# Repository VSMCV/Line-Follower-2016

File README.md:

# Line-Follower-2016
Hardware design and software files for a PID line follower robot.

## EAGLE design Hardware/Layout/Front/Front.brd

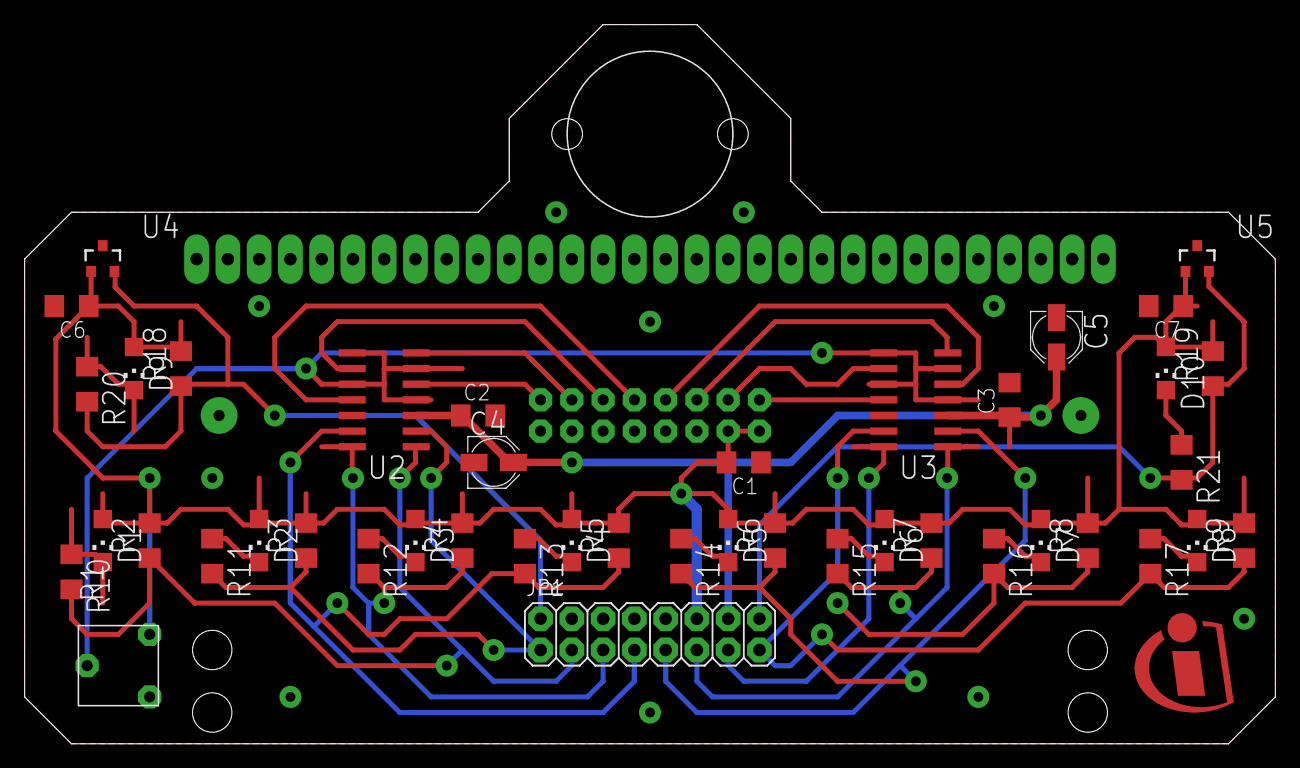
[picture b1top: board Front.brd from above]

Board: 2 copper layers, 101.6 x 58.4 mm, 47 parts (1 on the bottom side), 32 nets.

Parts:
BALL1: BALL
C1, C2, C3, C6, C7: C_NONPOL100NF; C1206
C4, C5: C-POL10UF; PANASONIC_B
D1, D2, D3, D4, D5, D6, D7, D8, D9, D10: LED; CHIPLED_1206
JP1: 2X08
JP2: 1X30
R1: R-TRIMMER; TRIMMER
R2, R3, R4, R5, R6, R7, R8, R9, R18, R19: 12k; R1206
R10, R11, R12, R13, R14, R15, R16, R17, R20, R21: 470R; R1206
U1: SENSOR_BAR_QTR-8ASENSOR_BAR; QTR-8A
U2, U3: LM339; SO14
U4, U5: TLE4964-6M; SOT23-3
U$1: INFINEON_LOGO_INFINEON_ICON_8

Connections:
+3V3: C1.2, C6.1, C7.1, D1.A, D2.A, D3.A, D4.A, D5.A, D6.A, D7.A, D8.A, D9.A, D10.A, JP1.12, R1.2, R2.2, R3.2, R4.2, R5.2, R6.2, R7.2, R8.2, R9.2, R18.2, R19.2, U1.P$2, U1.P$4, U4.1, U5.1
GND: C1.1, C2.2, C3.2, C4.-, C5.-, C6.2, C7.2, JP1.4, JP1.6, JP1.8, JP1.10, JP2.1, JP2.2, JP2.3, JP2.4, JP2.5, JP2.6, JP2.7, JP2.8, JP2.9, JP2.10, JP2.11, JP2.12, JP2.13, JP2.14, JP2.15, JP2.16, JP2.17, JP2.18, JP2.19, JP2.20, JP2.21, JP2.22, JP2.23, JP2.24, JP2.25, JP2.26, JP2.27, JP2.28, JP2.29, JP2.30, R1.1, U1.P$6, U1.P$8, U1.P$10, U1.P$12, U1.P$14, U1.P$16, U2.12, U3.12, U4.3, U5.3
LS1_IN: U1.P$15, U2.5
LS1_OUT: JP1.3, R2.1, R10.2, U2.1
LS2_IN: U1.P$13, U2.7
LS2_OUT: JP1.1, R3.1, R11.2, U2.2
LS3_IN: U1.P$11, U2.9
LS3_OUT: JP1.5, R4.1, R12.2, U2.14
LS4_IN: U1.P$9, U2.11
LS4_OUT: JP1.7, R5.1, R13.2, U2.13
LS5_IN: U1.P$7, U3.5
LS5_OUT: JP1.9, R6.1, R14.2, U3.2
LS6_IN: U1.P$5, U3.7
LS6_OUT: JP1.11, R7.1, R15.2, U3.1
LS7_IN: U1.P$3, U3.9
LS7_OUT: JP1.13, R8.1, R16.2, U3.14
LS8_IN: U1.P$1, U3.11
LS8_OUT: JP1.15, R9.1, R17.2, U3.13
MS1: JP1.2, R18.1, R20.2, U4.2
MS2: JP1.16, R19.1, R21.2, U5.2
unnamed: D1.C, R10.1
unnamed: D2.C, R11.1
unnamed: D3.C, R12.1
unnamed: D4.C, R13.1
unnamed: D5.C, R14.1
unnamed: D6.C, R15.1
unnamed: D7.C, R16.1
unnamed: D8.C, R17.1
unnamed: D10.C, R21.1
unnamed: D9.C, R20.1
REF: R1.3, U2.4, U2.6, U2.8, U2.10, U3.4, U3.6, U3.8, U3.10
V+: C2.1, C3.1, C4.+, C5.+, JP1.14, U2.3, U3.3

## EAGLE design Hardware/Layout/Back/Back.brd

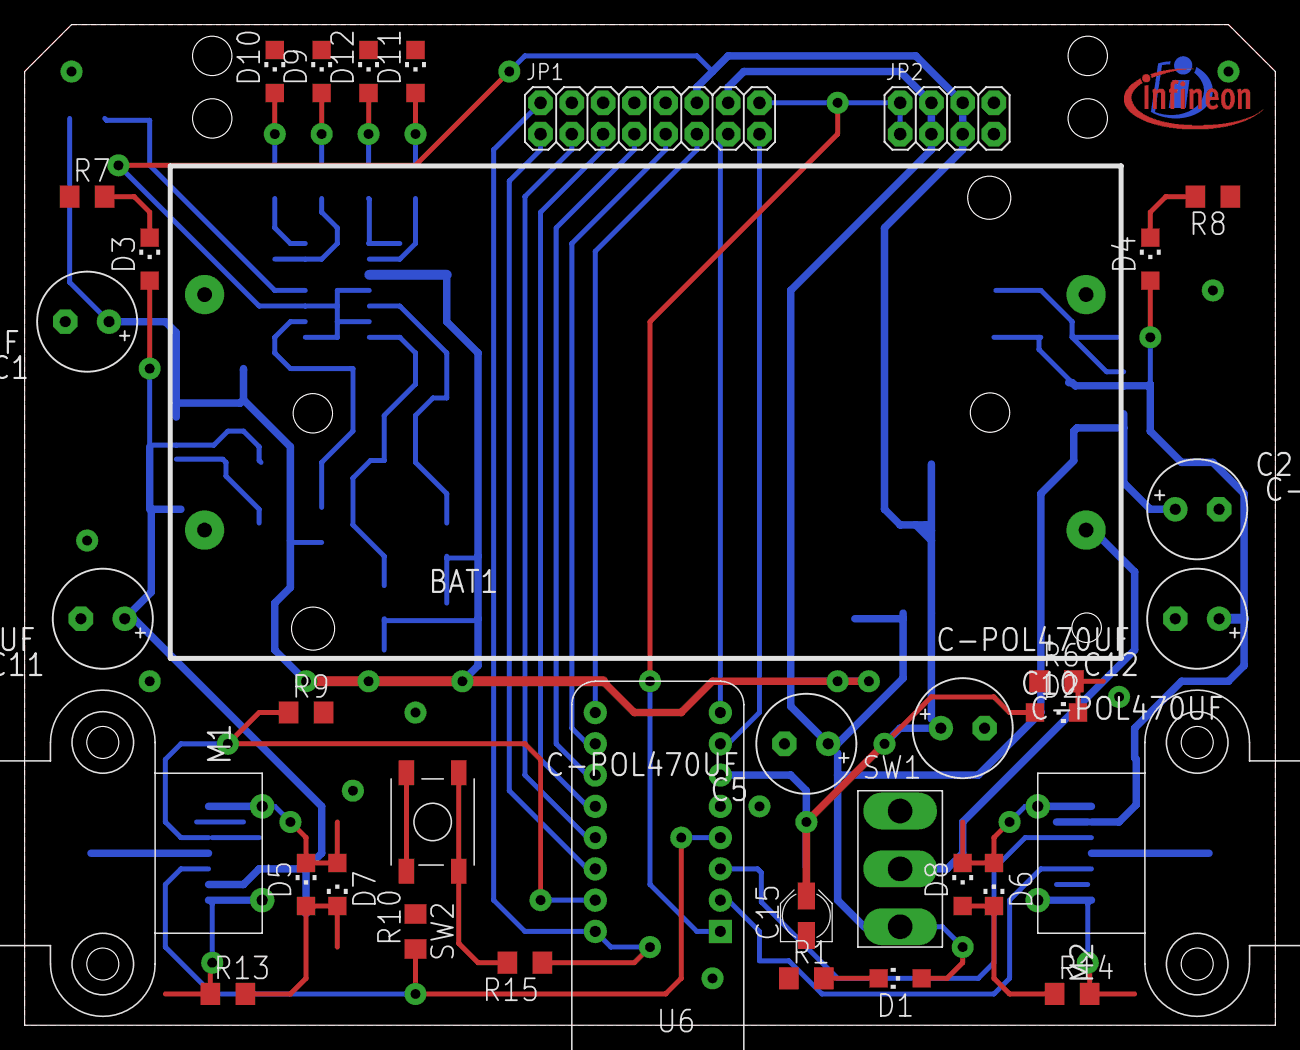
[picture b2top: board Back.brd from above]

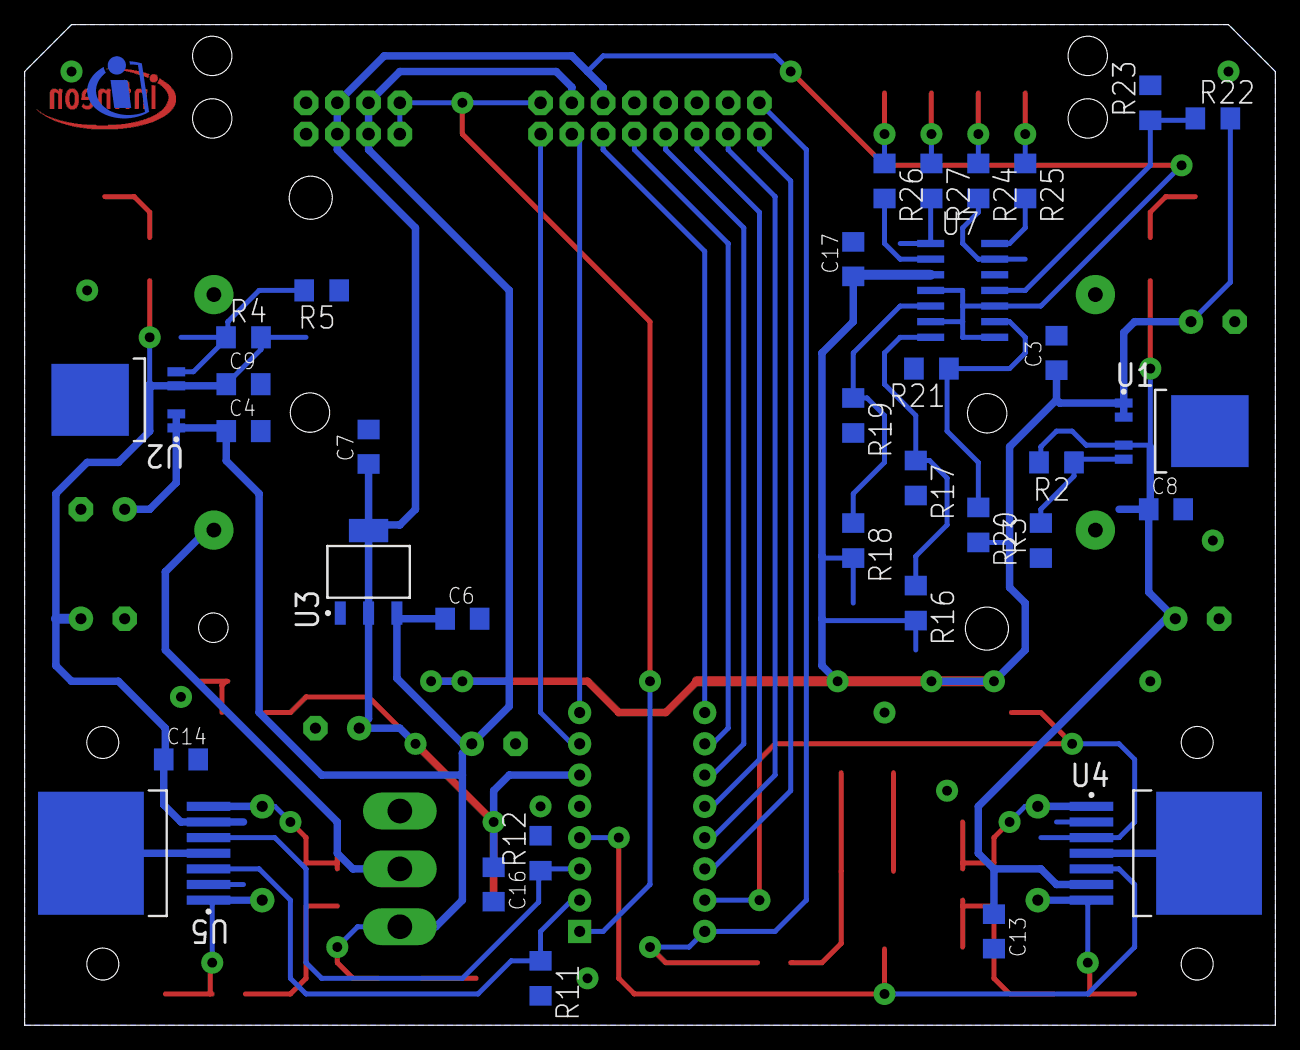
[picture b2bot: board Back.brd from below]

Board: 2 copper layers, 101.6 x 81.3 mm, 72 parts (35 on the bottom side), 45 nets.

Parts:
BAT1: BATTERY_HOLDER; BATT_SUPPORT_KEYSTONE
C1, C2, C5, C10, C11, C12: C-POL470UF; E3,5-8
C3, C4, C6, C7, C8, C9, C13, C14, C16, C17: C_NONPOL100NF; C1206
C15: C-POL10UF; PANASONIC_B
D1, D2, D3, D4, D5, D6, D7, D8, D9, D10, D11, D12: LED; CHIPLED_1206
JP1: 2X08
JP2: 2X04
M1, M2: MOTOR_PCBMOTOR; MICRO-MOTOR
R1, R6, R7, R8, R13, R14, R15, R24, R25, R26, R27: 470R; R1206
R2, R4, R22: 56k; R1206
R3, R5: 12k; R1206
R9, R10, R11, R12: 12K; R1206
R16: 51k; R1206
R17, R19, R21, R23: 43k; R1206
R18: 47k; R1206
R20: 62k; R1206
SW1: SWITCH1OFF2; MS111
SW2: PUSH_BUTTON_SMD; SWPB_SMD
U1, U2: TLF1963; INF-PG-TO252-5-11_L_1PRIMARY
U3: IFX8117ME_3V3; INF-PG-SOT223_SC-73_M_1PRIMARY
U4, U5: TLE5206; INF-PG-TO263-7-1_L_1PRIMARY
U6: XMC_2_GO
U7: LM339; SO14
U$1: INFINEON_LOGO_INFINEON_LOGO_5
U$2: INFINEON_LOGO_INFINEON_ICON_5

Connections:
8.4V: BAT1.+, SW1.P$2
+3V3: C7.1, C10.+, C15.+, C16.1, D2.A, JP1.12, JP2.5, JP2.6, U3.2, U3.4, U6.6, U7.4, U7.6, U7.8, U7.10
GND: BAT1.--, C1.-, C2.-, C3.2, C4.2, C5.-, C6.2, C7.2, C8.2, C9.2, C10.-, C11.-, C12.-, C13.2, C14.2, C15.-, C16.2, C17.2, D9.C, D10.C, D11.C, D12.C, JP1.4, JP1.6, JP1.8, JP1.10, JP2.7, JP2.8, R1.1, R3.1, R5.1, R6.1, R7.1, R8.1, R9.2, R10.2, R11.2, R12.2, R17.2, R19.2, R21.2, R23.2, SW2.P$1, SW2.P$2, U1.3, U2.3, U3.1, U4.4, U4.8, U5.4, U5.8, U6.5, U7.12
LS1: JP1.3, U6.13
LS2: JP1.1, U6.14
LS3: JP1.5, U6.12
LS4: JP1.7, U6.11
LS5: JP1.9, U6.10
LS6: JP1.11, U6.9
LS7: JP1.13, U6.8
LS8: JP1.15, U6.7
M1_IN1_DIG: R9.1, U4.3, U6.15
M1_IN2_PWM: R10.1, U4.5, U6.4
M2_IN1_DIG: R11.1, U5.3, U6.2
M2_IN2_PWM: R12.1, U5.5, U6.3
MS1: JP1.2, R15.1, U6.16
MS2: JP1.16, JP2.1, JP2.2, U6.1
unnamed: R2.1, R3.2, U1.5
unnamed: D1.C, R1.2
unnamed: D2.C, R6.2
unnamed: R4.1, R5.2, U2.5
unnamed: D4.C, R8.2
unnamed: D3.C, R7.2
unnamed: D5.C, D7.A, M1.M1, U4.1
unnamed: D5.A, D7.C, R13.2
unnamed: M1.M2, R13.1, U4.7
unnamed: D6.C, D8.A, R14.1
unnamed: M2.M1, R14.2, U5.1
unnamed: D6.A, D8.C, M2.M2, U5.7
unnamed: D10.A, R25.1
unnamed: R15.2, SW2.P$3, SW2.P$4
unnamed: R24.2, U7.13
unnamed: R25.2, U7.14
unnamed: R26.2, U7.2
unnamed: R27.2, U7.1
unnamed: D11.A, R26.1
unnamed: D12.A, R27.1
unnamed: D9.A, R24.1
unnamed: R16.1, R17.1, U7.7
unnamed: R18.1, R19.1, U7.5
unnamed: R20.1, R21.1, U7.9
unnamed: R22.1, R23.1, U7.11
V+: C1.+, C2.+, C3.1, C4.1, C5.+, C6.1, C17.1, D1.A, JP1.14, JP2.3, JP2.4, R16.2, R18.2, R20.2, R22.2, SW1.P$3, U1.1, U1.2, U2.1, U2.2, U3.3, U7.3
V+M1: C8.1, C11.+, C13.1, D3.A, R2.2, U1.4, U4.6
V+M2: C9.1, C12.+, C14.1, D4.A, R4.2, U2.4, U5.6

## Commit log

2017-09-07 initial
2019-01-10 Add back layout pic
2019-01-10 Add back schematic pic
2019-01-10 Add front schematic pic
2019-01-10 Add connector layout pic
2019-01-10 Add front layout pic
